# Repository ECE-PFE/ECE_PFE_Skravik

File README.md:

# (ECE) PFE Skravik

- Open a terminal in the project's folder
- Run `python restApi/main.py`
- Open the file `Interface/interface.html` in your browser.

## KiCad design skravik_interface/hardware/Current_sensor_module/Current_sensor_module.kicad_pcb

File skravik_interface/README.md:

# (ECE) PFE Skravik

- Open a terminal in the project's folder
- Run `python restApi/main.py`
- Open the file `public/interface.html` in your browser.

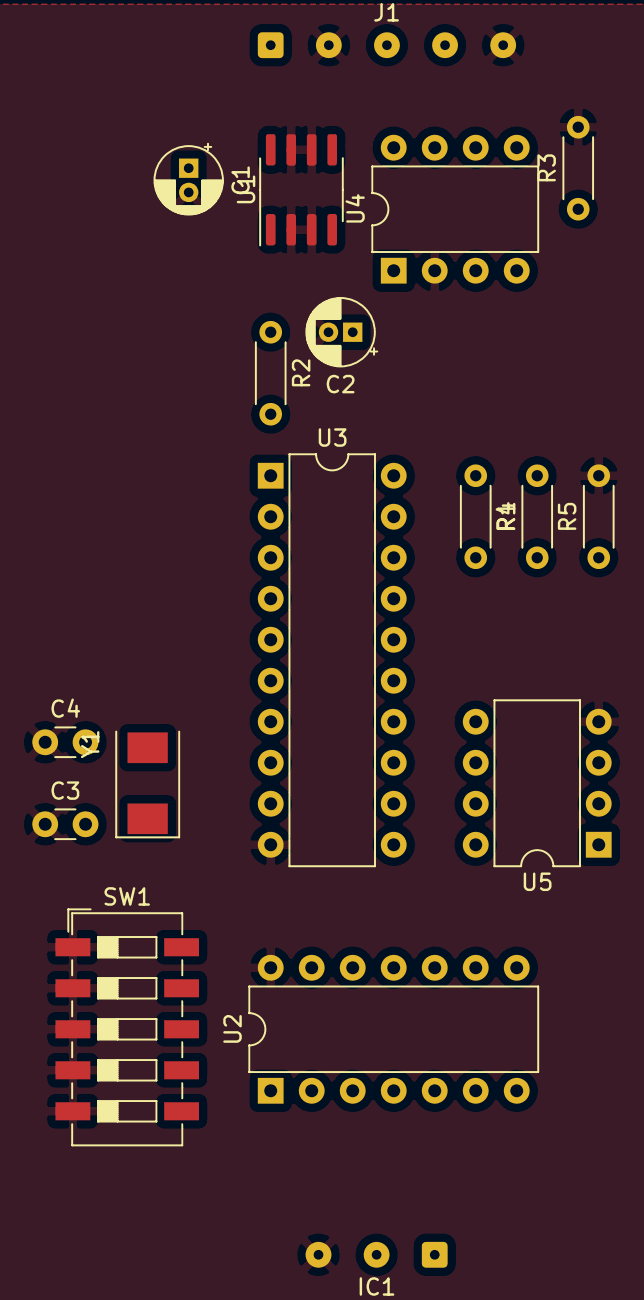
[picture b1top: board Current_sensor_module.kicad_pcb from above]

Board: 2 copper layers, 18 parts (0 on the bottom side), 25 nets, no tracks yet.

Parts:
C1: 0.33µF; CP_Radial_D4.0mm_P1.50mm
C2: 0.1µF; CP_Radial_D4.0mm_P1.50mm
C3, C4: 15pF; C_Disc_D3.0mm_W1.6mm_P2.50mm
IC1: CSLA2CD; SolderWire-0.1sqmm_1x03_P3.6mm_D0.4mm_OD1mm
J1: Conn_01x05; SolderWire-0.1sqmm_1x05_P3.6mm_D0.4mm_OD1mm
R1, R2, R3, R5: 10k; R_Axial_DIN0204_L3.6mm_D1.6mm_P5.08mm_Horizontal
R4: 14k; R_Axial_DIN0204_L3.6mm_D1.6mm_P5.08mm_Horizontal
SW1: SW_DIP_x05; SW_DIP_SPSTx05_Slide_6.7x14.26mm_W6.73mm_P2.54mm_LowProfile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
U1: L78L05_SO8; SOIC-8_3.9x4.9mm_P1.27mm
U2: ATtiny1614-SS; DIP-14_W7.62mm
U3: MCP2515-xSO; DIP-20_W7.62mm
U4: MCP2551-I-P; DIP-8_W7.62mm
U5: LMC6482; DIP-8_W7.62mm
Y1: 20MHz; Crystal_SMD_0603-2Pin_6.0x3.5mm

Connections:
+5V: C2.1, R1.1, R2.1, U1.1, U2.1, U3.20, U4.3, U5.8
+12V: C1.1, IC1.1, J1.1, U1.8
/CANH: J1.3, U4.7
/CANL: J1.4, U4.6
/Interrupt: U2.5, U3.13
/MISO: U2.12, U3.16
/MOSI: U2.11, U3.17
/SCK: U2.13, U3.14
/SS: U2.2, U3.18
/Sensor_In: U2.3, U5.1, U5.2
GND: C1.2, C2.2, C3.1, C4.1, IC1.3, J1.2, J1.5, R3.2, R5.2, SW1.1, SW1.2, SW1.3, SW1.4, SW1.5, U1.2, U1.3, U1.6, U1.7, U2.14, U3.10, U4.2, U5.4
unnamed: C3.2, U3.9, Y1.1
unnamed: C4.2, U3.8, Y1.2
unnamed: IC1.2, R4.1
unnamed: R1.2, U2.10
unnamed: R2.2, U3.19
unnamed: R3.1, U4.8
unnamed: R4.2, R5.1, U5.3
unnamed: SW1.6, U2.4
unnamed: SW1.7, U2.6
unnamed: SW1.8, U2.7
unnamed: SW1.9, U2.8
unnamed: SW1.10, U2.9
unnamed: U3.1, U4.1
unnamed: U3.2, U4.4

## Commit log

2020-10-13 rest api for json tests
2020-10-13 deleted log msgs
2020-10-13 affiche json
2020-10-13 bug correction
2020-10-13 maj periodique ok
2020-10-15 ajout de noms plus parlant (panneau solaire, moteur etc)
2020-10-23 readme updated
2020-11-24 interface juste le visuel
2020-11-24 ajout des productions et conso reelles
2020-11-24 bug fix
2020-12-01 interface update
2020-12-01 simple show detail example
2020-12-01 readme update
2020-12-01 tests
2020-12-08 Adaptation pour Skravik
2020-12-08 interface v2
2020-12-08 Ajout du script pour récupérer les données SignalK
2020-12-08 generation aleatoire plus coherentes
2020-12-08 update values with script python
2020-12-08 ajout fichier run
2020-12-09 update mise en page
2020-12-09 update print value detail
2021-01-06 fleche dynamique
2021-01-06 deleting old files
2021-01-06 new interface
2021-01-06 first prototype
2021-01-06 code formatted
2021-01-06 source done
2021-01-06 pages created
2021-01-06 sums added
2021-01-06 folder renamed
2021-01-06 new panneaux solaires page
2021-01-07 ajout alternateur et groupe eletrogene
2021-01-07 ajout modeles pages eoliennes et hydroliennes
2021-01-07 update detail panneau solaire
2021-01-07 maj pages eoliennes et hydroliennes
2021-01-07 code simplifie
2021-01-07 update detail eolienne
2021-01-07 random value generator updated
2021-01-07 bruh
2021-01-07 detail added to panneaux solaires
2021-01-07 panneaux solaires ok
2021-01-07 eoliennes et hydrolienne ok
2021-01-07 ajoute du pourcentage de batterie
2021-01-07 ajout de 1 decimale
2021-01-07 prototype
2021-01-08 new design
2021-01-08 design bug fix
2021-01-08 temporary bug fix
2021-01-08 pages groupe electrogene et alternateur ok
2021-01-08 ajout valeurs transferts
2021-01-08 ajout des valeurs sur les fleches
2021-01-11 ajout page parametre
2021-01-11 Ajout schéma capteur de courant
2021-01-11 Ajout package.json pour SignalK
2021-01-11 creation fichier css
2021-01-11 Adaptation pour SignalK
2021-01-11 ajout slider
2021-01-11 usage de localstorage
2021-01-11 ajout icone warning
2021-01-12 amelioration page avertisement
2021-01-12 ajout anemometre
2021-01-12 utilisation de flex et space-evenly
2021-01-12 amelioration sliders
2021-01-12 reorganisation code
2021-01-12 nouvelle fonction de recuperation des donnees
2021-01-12 premiere alerte fonctionnelle
2021-01-12 page avertissement fonctionnelle
2021-01-12 maj alertes
2021-01-12 utilisation css
2021-01-12 suppression fichier inutile
2021-01-12 simplification du js
2021-01-12 ajout de parametres
2021-01-13 reorganisation
2021-01-13 Modification package.json
2021-01-13 ajout pile a hydrogene
2021-01-13 Suppression dossier lib + ajout d'un script exemple pour Websocket avec SignalK
2021-01-13 Image en bleu + Alerte gi
2021-01-13 Ajout de variables globales pour la connexion à l'API SignalK
2021-01-13 ajout de toutes les alertes
2021-01-13 Thermomètre Anémomètre Vitesse
2021-01-13 alertes fontionelles
2021-01-13 interface simulation
2021-01-13 Modification des chemins
2021-01-13 Fix conflicts
2021-01-13 utilisation des icones alertes
2021-01-13 simulation update
2021-01-13 icone alerte eolienne ok
2021-01-14 Suppression de l'interface de simulation + correction pathSsignalK
2021-01-14 Integration de l'interface de simulation à SignalK
2021-01-14 bug fix : le js ne plante plus sil manque une donnee
2021-01-14 plus darrondis
2021-01-14 Correction faute de frappe
2021-01-14 Correction erreur nom attribute
2021-01-14 add admin
2021-01-14 icones alertes ok
2021-01-14 correction des donnees affichees
2021-01-14 old readme deleted
2021-01-15 restApi deleted
2021-01-15 somme bug fix
2021-01-15 valeurs de transferts ok
2021-01-15 data pour les warnings actualisee
2021-01-15 utilisation de let var et const
2021-01-15 carte update
2021-01-15 ajout des previsions
2021-01-15 ajout somme prev
2021-01-15 ajout image thermometre
2021-01-18 Modification formulaire carte.html
2021-01-18 Remplacement de carte.html vers public/index.html
2021-01-18 Liaison interface skravik_admin avec plugin
2021-01-18 Liaison plugin avec interface
2021-01-19 Correction calcul de la production prévisionnelle des éoliennes et panneaux solaires
2021-01-19 Ajout TODO.txt
2021-01-19 Modification texte prévision et unité en kWh
2021-01-19 Ajout dans TODO.txt
2021-01-20 page equipement
2021-01-20 Modification configuration plugin pour ajout des consommateurs
2021-01-20 Correction ajout de consommateurs
2021-01-20 Découpage des différentes pages en fonctions
2021-01-20 Modification de la page panneaux solaires pour la rendre dynamique
2021-01-20 Modification de la page eoliennes pour la rendre dynamique
2021-01-20 Modification de la page hydroliennes pour la rendre dynamique
2021-01-21 Indentation
2021-01-21 Modification de la page groupe electrogène/alternateurs/pile à combustible pour la rendre dynamique
2021-01-21 add equipement
2021-01-21 fix bug
2021-01-21 Modification de la simulation + ajout de tous les consommateur Cordialement.
2021-01-21 Modification des warnings pour les rendre dynamique
2021-01-21 Correction et modification du chemin pour les consommateurs
2021-01-22 Correction des id + Adaptation des sommes
2021-01-22 Ajout des moteurs
2021-01-22 Ajout des moteurs en dynamique
2021-01-22 Correction : Remplacement de variables globales par des variables locales
2021-01-22 Ajout moteur dans l'interface de simulation
2021-01-22 Ajout moteur dans l'interface simulation
2021-01-22 Ajout gestion des sommes de consommation du moteur
2021-01-22 Fix div_categorie is null lorsque que l'on n'a pas ajouté de consommateurs dans la config admin
2021-01-22 Ajout des producteurs dans la configuration du plugin admin
2021-01-22 Fix nom de la propriété 'categorie' en 'category'
2021-01-22 Modification path producteurs dans skravik sim + suppression de la propriété technology
2021-01-22 Ajout des batteries dans la configuration du plugin admin
2021-01-22 Ajout des batteries dans la simulation
2021-01-22 Ajout api_key_2 + correction unité kW en W + suppression de l'affichage de prévision pour certains producteurs
2021-01-23 Modification : Calcul prévisionnel de la production horaire éolienne et solaire
2021-01-23 Ajout des graphiques
2021-01-25 ajout message enregistre
2021-01-25 Modification du graphique de prévision à +48h
2021-01-25 nouvelle image
2021-01-25 suppression ancien fichier
2021-01-25 Modification du titre du graphique
2021-01-25 Ajout d'un formulaire pour saisir la latitude et la longitude
2021-01-25 ajout message calcul en cours
2021-01-26 Amélioration de la prédiction de production solaire
2021-01-26 Corrections diverses + Suppression de quelques consoles.log
2021-01-26 ajout preconfiguration
2021-01-26 ajout alerte surconsommation
2021-01-26 ajout alerte batterie faible
2021-01-27 Ajout des infos de temperature, vitesse, etc...
2021-01-27 Correction affichage du message d'alerte
2021-01-27 Ajout production J+1 moyenne + adaptation dynamique pour les alertes HYD, PHG et BATTERY
2021-01-27 Ajout des nouveaux messages et interface dans le simulateur
2021-01-28 Correction nom de chemin
2021-01-28 Ajout image batterie_alerte.gif
2021-01-28 Modification nom du package skravik_interface + Modification config du plugin
2021-01-28 Modification readme
2021-01-28 Modification nom de variables et commentaires
2021-01-28 Ajout d'une fonction de récupération de la configuration du plugin et petite correction
2021-01-28 Modification : Les producteurs/batteries/consommateurs s'actualisent en fonction de la configuration du plugin uniquement
2021-01-29 Correction somme
2021-01-29 Modification : Valeur par défaut dans le simulateur
2021-01-29 Modification : Titre section de la configuration du plugin + readme
2021-01-29 Corrections alertes
2021-02-05 Fusion de skravik_admin et skravik_interface
2021-02-05 Correction nom plugin
